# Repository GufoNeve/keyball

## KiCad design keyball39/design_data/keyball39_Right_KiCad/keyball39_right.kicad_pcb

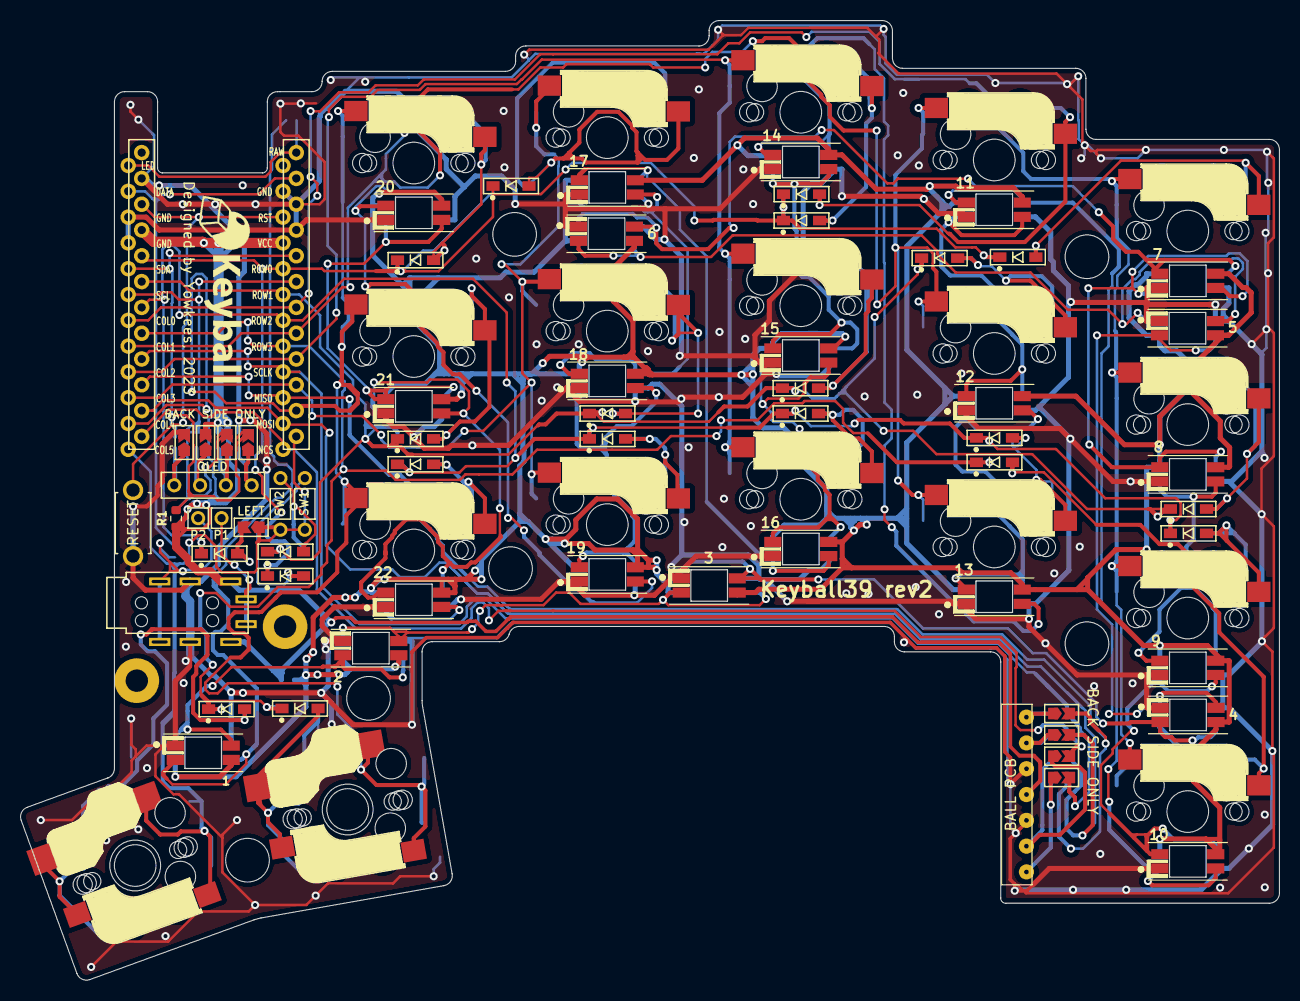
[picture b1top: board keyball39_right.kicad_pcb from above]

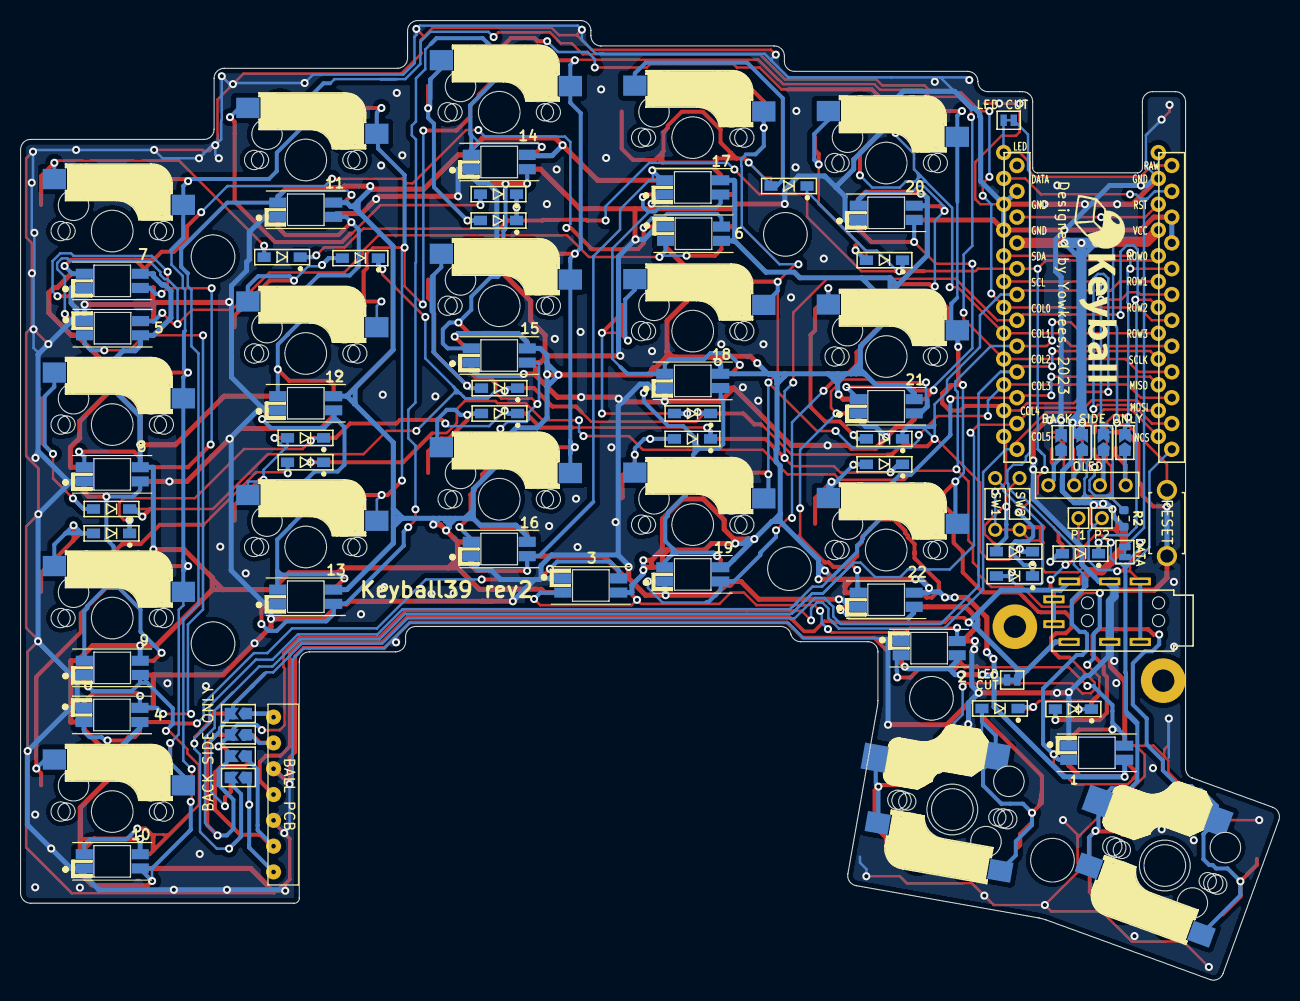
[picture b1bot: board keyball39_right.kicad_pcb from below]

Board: 2 copper layers, 123.9 x 94.5 mm, 102 parts (13 on the bottom side), 75 nets.

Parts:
1, 2, 3, 4, 5, 6: YS-SK6812MINI-E; YS-SK6812MINI-Keyball-BL
7, 8, 9, 10, 11, 12, 13, 14, 15, 16, 17, 18, 19, 20, 21, 22: YS-SK6812MINI-E; YS-SK6812MINI-Keyball-TL
D1, D2, D3, D4, D5, D6, D7, D8, D9, D10, D11, D12, D13, D14, D15, D16, D17, D18, D19, D20, D21: D; D3_SMD_v2_BOTH
G1, G2: LOGO; keyball_logo700
J1: OLED
J2: BALL_PCB; Mac8_L_7pin_contact_NEW2023
J3, J4: Conn_01x01-Connector_Generic; MountingHole_2.2mm_M2_Pad
J5, J6, J7, J8, J9, J10: Conn_01x01-Connector_Generic; MountingHole_4.3mm_M4
J11: TRS_JACK; TRRS_JACK_MJ4PP9
JP1: LEFT; Jumper_NEW_BIG
JP2, JP3, JP4, JP5, JP6, JP7, JP8, JP9, JP10, JP11, JP12, JP13, JP14, JP15, JP16, JP17: Device_Jumper_NO_Small; Jumper_NEW_BIG
JP20: DATA; JP025
LED: CUT; JP05
LED CUT: Device_Jumper_NO_Small; JP025
P1, P2: I2C; 1pin_conn
R3, R4: PULL_UP; R_0603_1608Metric
SW1, SW2: PULL_UP; R
SW1#2, SW2#2, SW3, SW4, SW5, SW6, SW7, SW8, SW9, SW10, SW11, SW12, SW13, SW14, SW15, SW16: SW_PUSH-kbd; CherryMX_MidHeight_Hotswap
SW17, SW18: SW_PUSH-kbd; MX&Choc_V1_V2_Hotswap_BOTH
SW19: RESET_SW; ResetSW
U1: ProMicro-kbd; ProMicro_v2

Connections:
COL0: SW1#2.1, SW6.1, SW11.1, SW16.1, U1.7
COL1: SW2#2.1, SW7.1, SW12.1, U1.8
COL2: SW3.1, SW8.1, SW13.1, U1.9
COL3: SW4.1, SW9.1, SW14.1, U1.10
COL4: SW5.1, SW10.1, SW15.1, SW17.1, U1.11
COL5: JP1.1, SW1.1, SW2.1, SW18.1, U1.12
DATA: JP20.2, U1.2
GND: 1.3, 2.3, 3.3, 4.3, 5.3, 6.3, 7.3, 8.3, 9.3, 10.3, 11.3, 12.3, 13.3, 14.3, 15.3, 16.3, 17.3, 18.3, 19.3, 20.3, 21.3, 22.3, J2.3, J2.5, J11.C, JP3.2, JP17.2, SW19.2, U1.3, U1.4, U1.23
LED: LED CUT.1, U1.1
MISO: JP2.2, JP16.2, U1.15
MOSI: JP4.2, JP14.2, U1.14
NCS: JP6.2, JP12.2, U1.13
unnamed: D1.2, SW1#2.2
unnamed: D2.2, SW2#2.2
unnamed: D3.2, SW3.2
unnamed: D4.2, SW4.2
unnamed: D5.2, SW5.2
unnamed: D6.2, SW1.2
unnamed: D7.2, SW6.2
unnamed: D8.2, SW7.2
unnamed: D9.2, SW8.2
unnamed: D10.2, SW9.2
unnamed: D11.2, SW10.2
unnamed: D12.2, SW2.2
unnamed: D13.2, SW11.2
unnamed: D14.2, SW12.2
unnamed: D15.2, SW13.2
unnamed: D16.2, SW14.2
unnamed: D17.2, SW15.2
unnamed: D18.2, JP1.2
unnamed: D19.2, SW16.2
unnamed: D20.2, SW17.2
unnamed: D21.2, SW18.2
unnamed: J1.1, JP3.1, JP11.1
unnamed: J1.2, JP5.1, JP13.1
unnamed: J1.3, JP7.1, JP15.1
unnamed: J1.4, JP9.1, JP17.1
unnamed: J2.1, JP2.1, JP10.1
unnamed: J2.2, JP4.1, JP12.1
unnamed: J2.6, JP6.1, JP14.1
unnamed: J2.7, JP8.1, JP16.1
unnamed: J11.A, P1.1
unnamed: J11.B, JP20.1, P2.1
unnamed: 1.1, 2.1, 3.1, 4.1, 5.1, 6.1, 7.1, 8.1, 9.1, 10.1, 11.1, 12.1, 13.1, 14.1, 15.1, 16.1, 17.1, 18.1, 19.1, 20.1, 21.1, 22.1, LED.1
unnamed: 1.4, LED CUT.2
unnamed: 1.2, 2.4
unnamed: 2.2, 3.4
unnamed: 3.2, 4.4
unnamed: 4.2, 5.4
unnamed: 5.2, 6.4
unnamed: 6.2, 7.4
unnamed: 7.2, 8.4
unnamed: 8.2, 9.4
unnamed: 10.2, 11.4
unnamed: 9.2, 10.4
unnamed: 11.2, 12.4
unnamed: 12.2, 13.4
unnamed: 13.2, 14.4
unnamed: 14.2, 15.4
unnamed: 15.2, 16.4
unnamed: 16.2, 17.4
unnamed: 17.2, 18.4
unnamed: 18.2, 19.4
unnamed: 19.2, 20.4
unnamed: 20.2, 21.4
unnamed: 21.2, 22.4
RESET: SW19.1, U1.22
ROW0: D1.1, D2.1, D3.1, D4.1, D5.1, D6.1, U1.20
ROW1: D7.1, D8.1, D9.1, D10.1, D11.1, D12.1, U1.19
ROW2: D13.1, D14.1, D15.1, D16.1, D17.1, D18.1, U1.18
ROW3: D19.1, D20.1, D21.1, U1.17
SCL: JP7.2, JP13.2, R4.2, U1.6
SCLK: JP8.2, JP10.2, U1.16
SDA: JP9.2, JP11.2, R3.2, U1.5
VCC: J2.4, J11.D, JP5.2, JP15.2, LED.2, R3.1, R4.1, U1.21

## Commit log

2024-08-01 20240801
2024-09-07 いつのだ
